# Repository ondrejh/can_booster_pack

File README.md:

can_booster_pack
================

Launchpad (TI) CAN bus booster pack

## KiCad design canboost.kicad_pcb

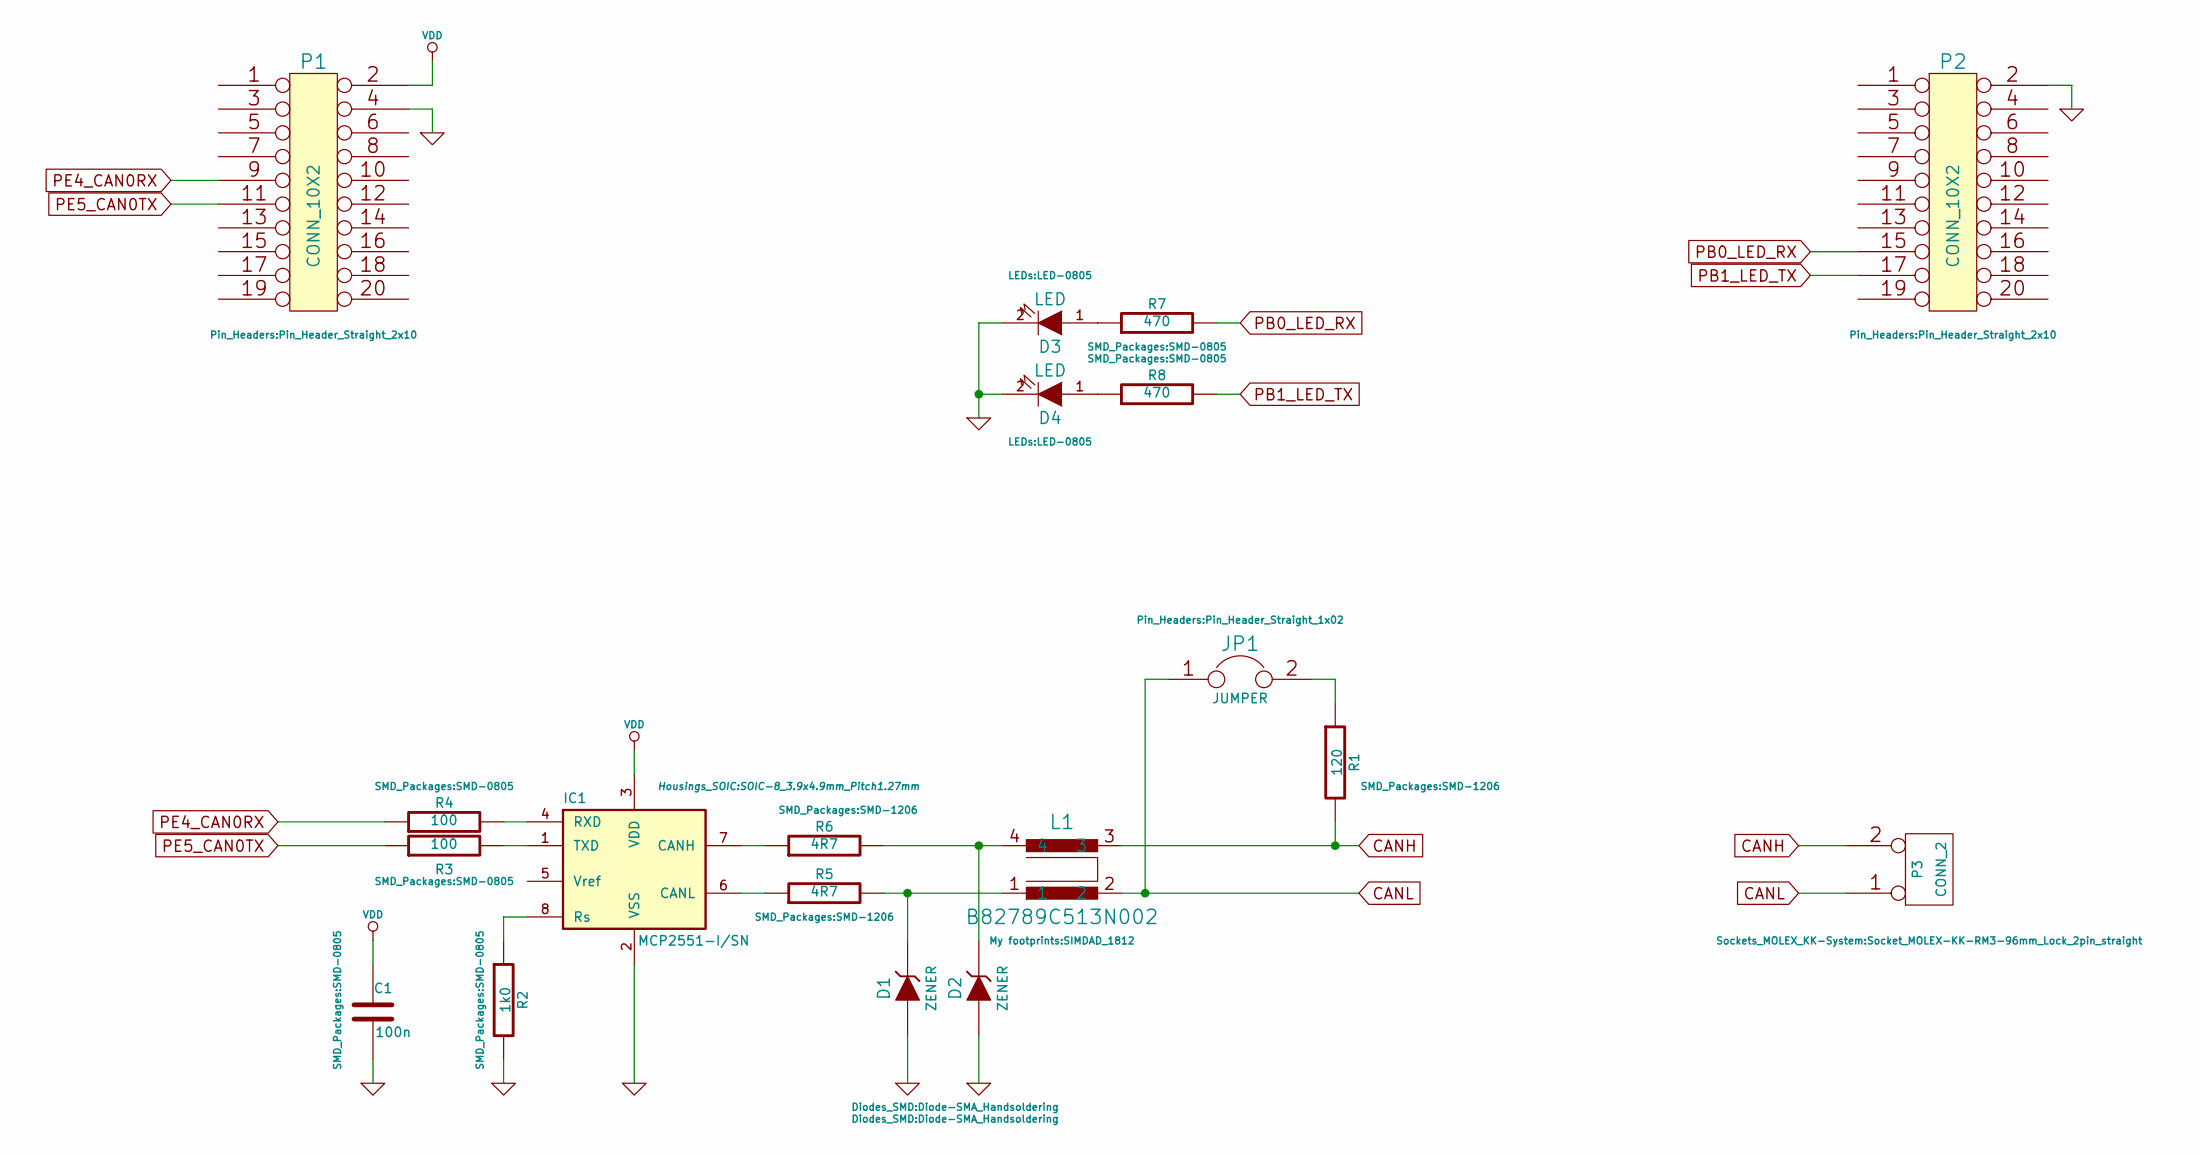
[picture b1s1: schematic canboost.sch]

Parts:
C1: 100n; SMD-0805
D1, D2: ZENER; Diode-SMA_Handsoldering
D3, D4: LED; LED-0805
IC1: MCP2551-I/SN; SOIC-8_3.9x4.9mm_Pitch1.27mm
JP1: JUMPER; Pin_Header_Straight_1x02
L1: B82789C513N002; SIMDAD_1812
P1, P2: CONN_10X2; Pin_Header_Straight_2x10
P3: CONN_2; Socket_MOLEX-KK-RM3-96mm_Lock_2pin_straight
R1: 120; SMD-1206
R2: 1k0; SMD-0805
R3, R4: 100; SMD-0805
R5, R6: 4R7; SMD-1206
R7, R8: 470; SMD-0805

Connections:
CANH: L1.3, P3.2 (PM), R1.2
CANL: JP1.1, L1.2, P3.1
GND: C1.2, D1.1 (A), D2.1 (A), D3.2 (K), D4.2 (K), IC1.2 (VSS), P1.4, P2.2, R2.2
unnamed: D1.2 (K), L1.1, R5.2
unnamed: D2.2 (K), L1.4, R6.2
unnamed: D3.1 (A), R7.1
unnamed: D4.1 (A), R8.1
unnamed: IC1.1 (TXD), R3.2
unnamed: IC1.4 (RXD), R4.2
unnamed: IC1.6 (CANL), R5.1
unnamed: IC1.7 (CANH), R6.1
unnamed: IC1.8 (Rs), R2.1
unnamed: JP1.2, R1.1
PB0_LED_RX: P2.15, R7.2
PB1_LED_TX: P2.17, R8.2
PE4_CAN0RX: P1.9, R4.1
PE5_CAN0TX: P1.11, R3.1
VDD: C1.1, IC1.3 (VDD), P1.2

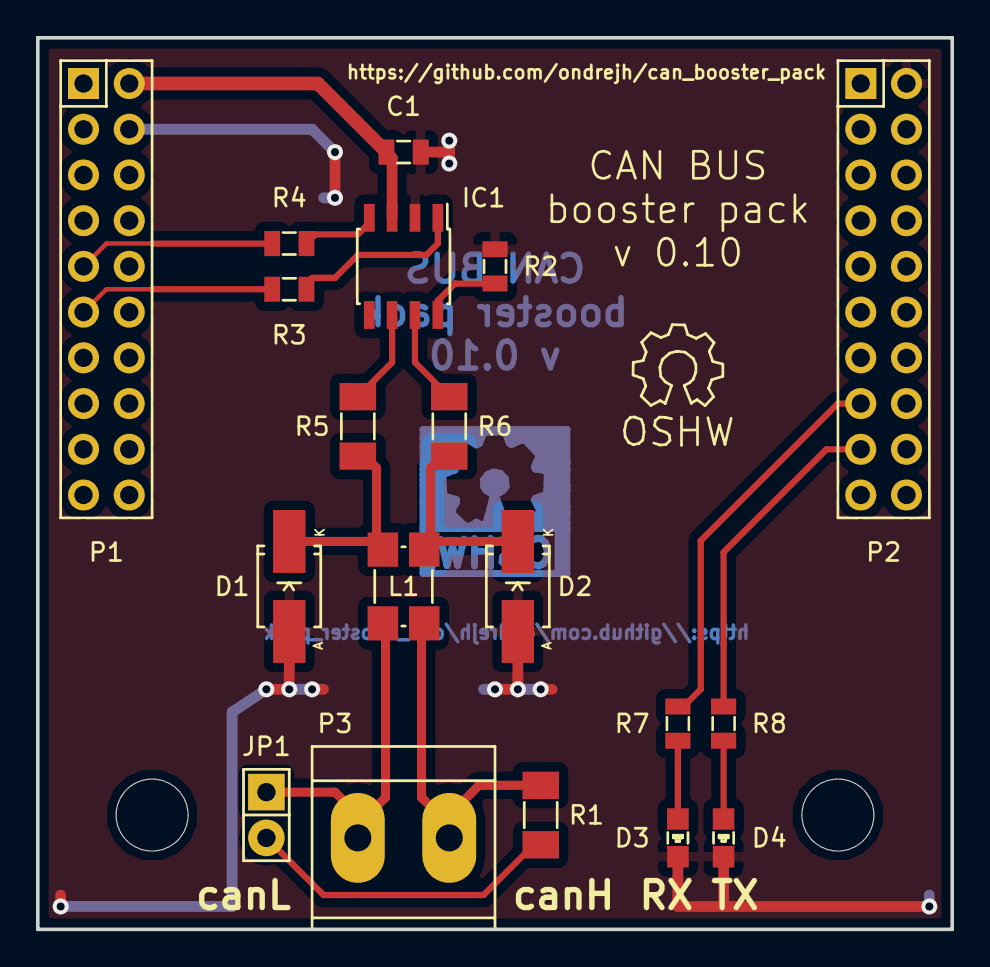
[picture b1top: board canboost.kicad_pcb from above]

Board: 2 copper layers, 50.8 x 49.5 mm, 23 parts (1 on the bottom side), 18 nets.

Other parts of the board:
MH: MountingHole_4mm_RevA_Date21Jun2010; MountingHole_4mm
MH#2: MountingHole_4mm_RevA_Date21Jun2010; MountingHole_4mm
SYM: Symbol_OSHW-Logo_SilkScreen_07Jul2012; Symbol_OSHW-Logo_SilkScreen
SYM#2: Symbol_OSHW-Logo_CopperTop_Negative_07Jul2012; Symbol_OSHW-Logo_CopperTop_Negative

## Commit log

2014-11-21 raw schematic
2014-11-21 dummy project form TivaWare added (as a base for future fw)
2014-11-21 schematic seems to be finished
2014-11-29 changed to tiva c target
2014-11-29 code:blocks project file
2014-12-05 netlist, footprint assigned
2014-12-06 layout complete (v0.10)
2014-12-19 one logo, some text ..
2014-12-22 debug uart
2014-12-22 can RX interrupt
2015-01-05 message output simlified
2015-01-09 3d models, silk screen
2015-01-09 gerber files!
2015-01-12 order form not to be versioned (published)
2015-01-12 rendered board image
2015-01-12 board image (first markdown trial)
2015-01-19 system tick timer value (TIMER0_A)
2015-01-20 some timer tuning
2015-01-20 only one timestamp
2015-02-02 rx led timing
2015-04-10 script: make program_win
2015-04-10 translation trial
2015-04-10 postfinal changes
2015-04-13 uart rx buffer
2018-03-28 ahellalotofchanges from past
2018-03-28 receive and decode function
2018-03-29 ignore list update
2018-03-29 decoder with message content resolving
2018-08-07 speed change
2018-08-07 generic filter and some testing
2018-08-07 some error handling
